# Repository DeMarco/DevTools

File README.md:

# DevTools
Small projects that help get bigger projects be developped more easily

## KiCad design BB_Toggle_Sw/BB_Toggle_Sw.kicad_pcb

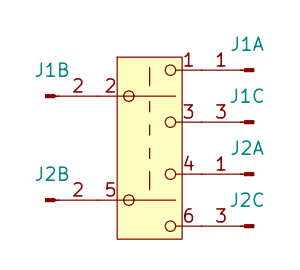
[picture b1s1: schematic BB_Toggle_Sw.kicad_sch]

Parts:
J1, J2: Conn_01x03_PinHeader; PinHeader_1x03_P2.54mm_Vertical
SW1: SW_DPDT_OnOffOn; Toggle_Switch_2_Poles_TE

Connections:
unnamed: J1.1, SW1.1 (A)
unnamed: J1.2, SW1.2 (B)
unnamed: J1.3, SW1.3 (C)
unnamed: J2.1, SW1.4 (A)
unnamed: J2.2, SW1.5 (B)
unnamed: J2.3, SW1.6 (C)

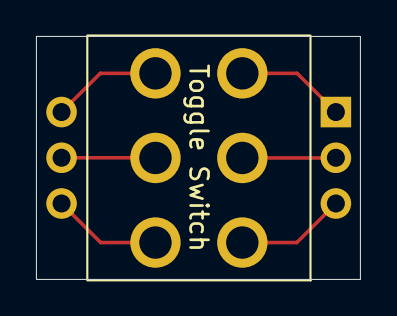
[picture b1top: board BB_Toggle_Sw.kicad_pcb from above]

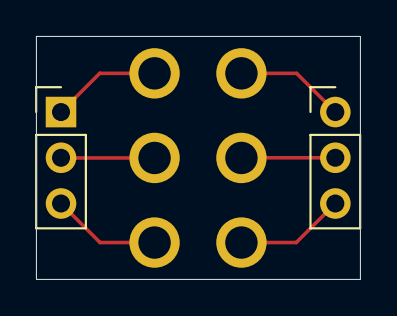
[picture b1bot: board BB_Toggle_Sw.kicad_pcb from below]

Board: 2 copper layers, 18.0 x 13.5 mm, 3 parts (2 on the bottom side), 6 nets.

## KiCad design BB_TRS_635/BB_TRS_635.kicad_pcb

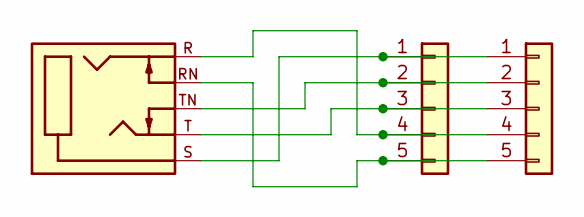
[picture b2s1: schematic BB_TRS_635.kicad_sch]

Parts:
J1, J2: Conn_01x05; PinHeader_1x05_P2.54mm_Vertical
J3: TRS_Jack_6.35mm_Sw; CUI_SJ-63083D

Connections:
unnamed: J1.1, J2.1, J3.S (1)
unnamed: J1.2, J2.2, J3.TN (2)
unnamed: J1.3, J2.3, J3.T (3)
unnamed: J1.4, J2.4, J3.R (4)
unnamed: J1.5, J2.5, J3.RN (5)

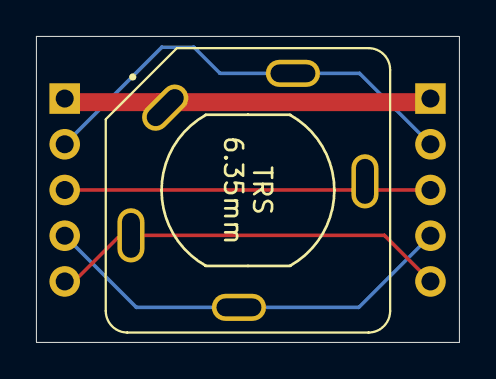
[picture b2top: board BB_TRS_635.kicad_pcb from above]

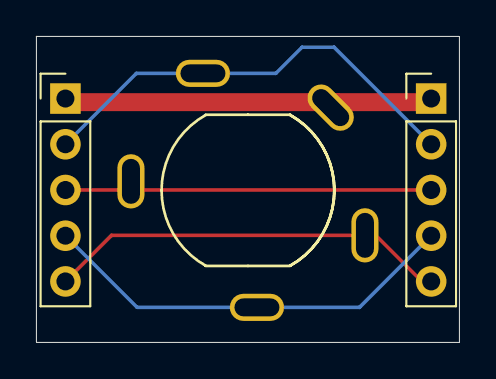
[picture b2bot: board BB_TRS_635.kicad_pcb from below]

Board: 2 copper layers, 23.5 x 17.0 mm, 3 parts (2 on the bottom side), 5 nets.

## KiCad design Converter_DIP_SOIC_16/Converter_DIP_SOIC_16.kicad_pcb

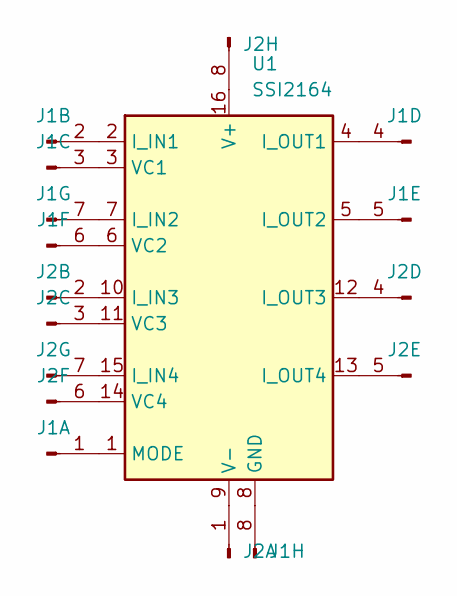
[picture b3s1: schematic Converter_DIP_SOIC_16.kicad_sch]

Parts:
J1, J2: Conn_01x08_PinHeader; PinHeader_1x08_P2.54mm_Vertical
U1: SSI2164; SOIC-16_3.9x9.9mm_P1.27mm

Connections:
unnamed: J1.1, U1.1 (MODE)
unnamed: J1.2, U1.2 (I_IN1)
unnamed: J1.3, U1.3 (VC1)
unnamed: J1.4, U1.4 (I_OUT1)
unnamed: J1.5, U1.5 (I_OUT2)
unnamed: J1.6, U1.6 (VC2)
unnamed: J1.7, U1.7 (I_IN2)
unnamed: J1.8, U1.8 (GND)
unnamed: J2.1, U1.9 (V-)
unnamed: J2.2, U1.10 (I_IN3)
unnamed: J2.3, U1.11 (VC3)
unnamed: J2.4, U1.12 (I_OUT3)
unnamed: J2.5, U1.13 (I_OUT4)
unnamed: J2.6, U1.14 (VC4)
unnamed: J2.7, U1.15 (I_IN4)
unnamed: J2.8, U1.16 (V+)

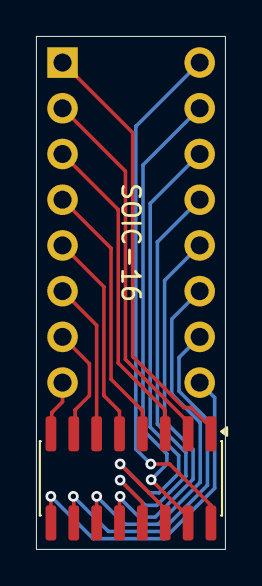
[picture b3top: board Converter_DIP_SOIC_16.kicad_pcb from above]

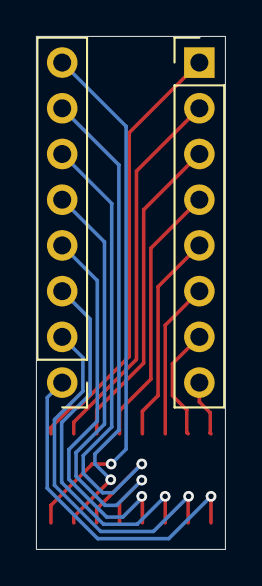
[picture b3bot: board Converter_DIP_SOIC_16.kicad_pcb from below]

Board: 2 copper layers, 10.5 x 28.5 mm, 3 parts (2 on the bottom side), 16 nets.

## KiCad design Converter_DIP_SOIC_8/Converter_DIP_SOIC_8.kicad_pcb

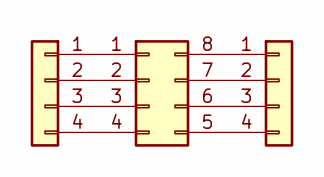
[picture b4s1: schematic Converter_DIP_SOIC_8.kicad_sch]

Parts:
J1, J2: Conn_01x04; PinHeader_1x04_P2.54mm_Vertical
J3: Conn_02x04_Counter_Clockwise; SOIC-8_3.9x4.9mm_P1.27mm

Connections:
unnamed: J1.1, J3.1
unnamed: J1.2, J3.2
unnamed: J1.3, J3.3
unnamed: J1.4, J3.4
unnamed: J2.1, J3.8
unnamed: J2.2, J3.7
unnamed: J2.3, J3.6
unnamed: J2.4, J3.5

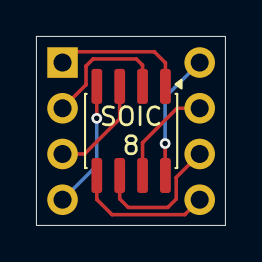
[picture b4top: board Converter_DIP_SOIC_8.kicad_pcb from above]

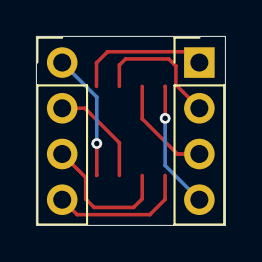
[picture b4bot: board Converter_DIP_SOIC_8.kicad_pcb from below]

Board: 2 copper layers, 10.5 x 10.5 mm, 3 parts (2 on the bottom side), 8 nets.

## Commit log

2026-06-23 SOIC 16 converter design in progress
2026-06-23 Designed SOIC 16 and SSOP 10 DIP converters
2026-06-23 Designed DIP SOIC 16 converter
2026-06-24 Designed SOIC8 and SSOP10 converters to DIP
2026-06-24 Designed TRS jack and Toggle Switch BB helpers
2026-06-25 Corrected text on Toggle Sw BB
